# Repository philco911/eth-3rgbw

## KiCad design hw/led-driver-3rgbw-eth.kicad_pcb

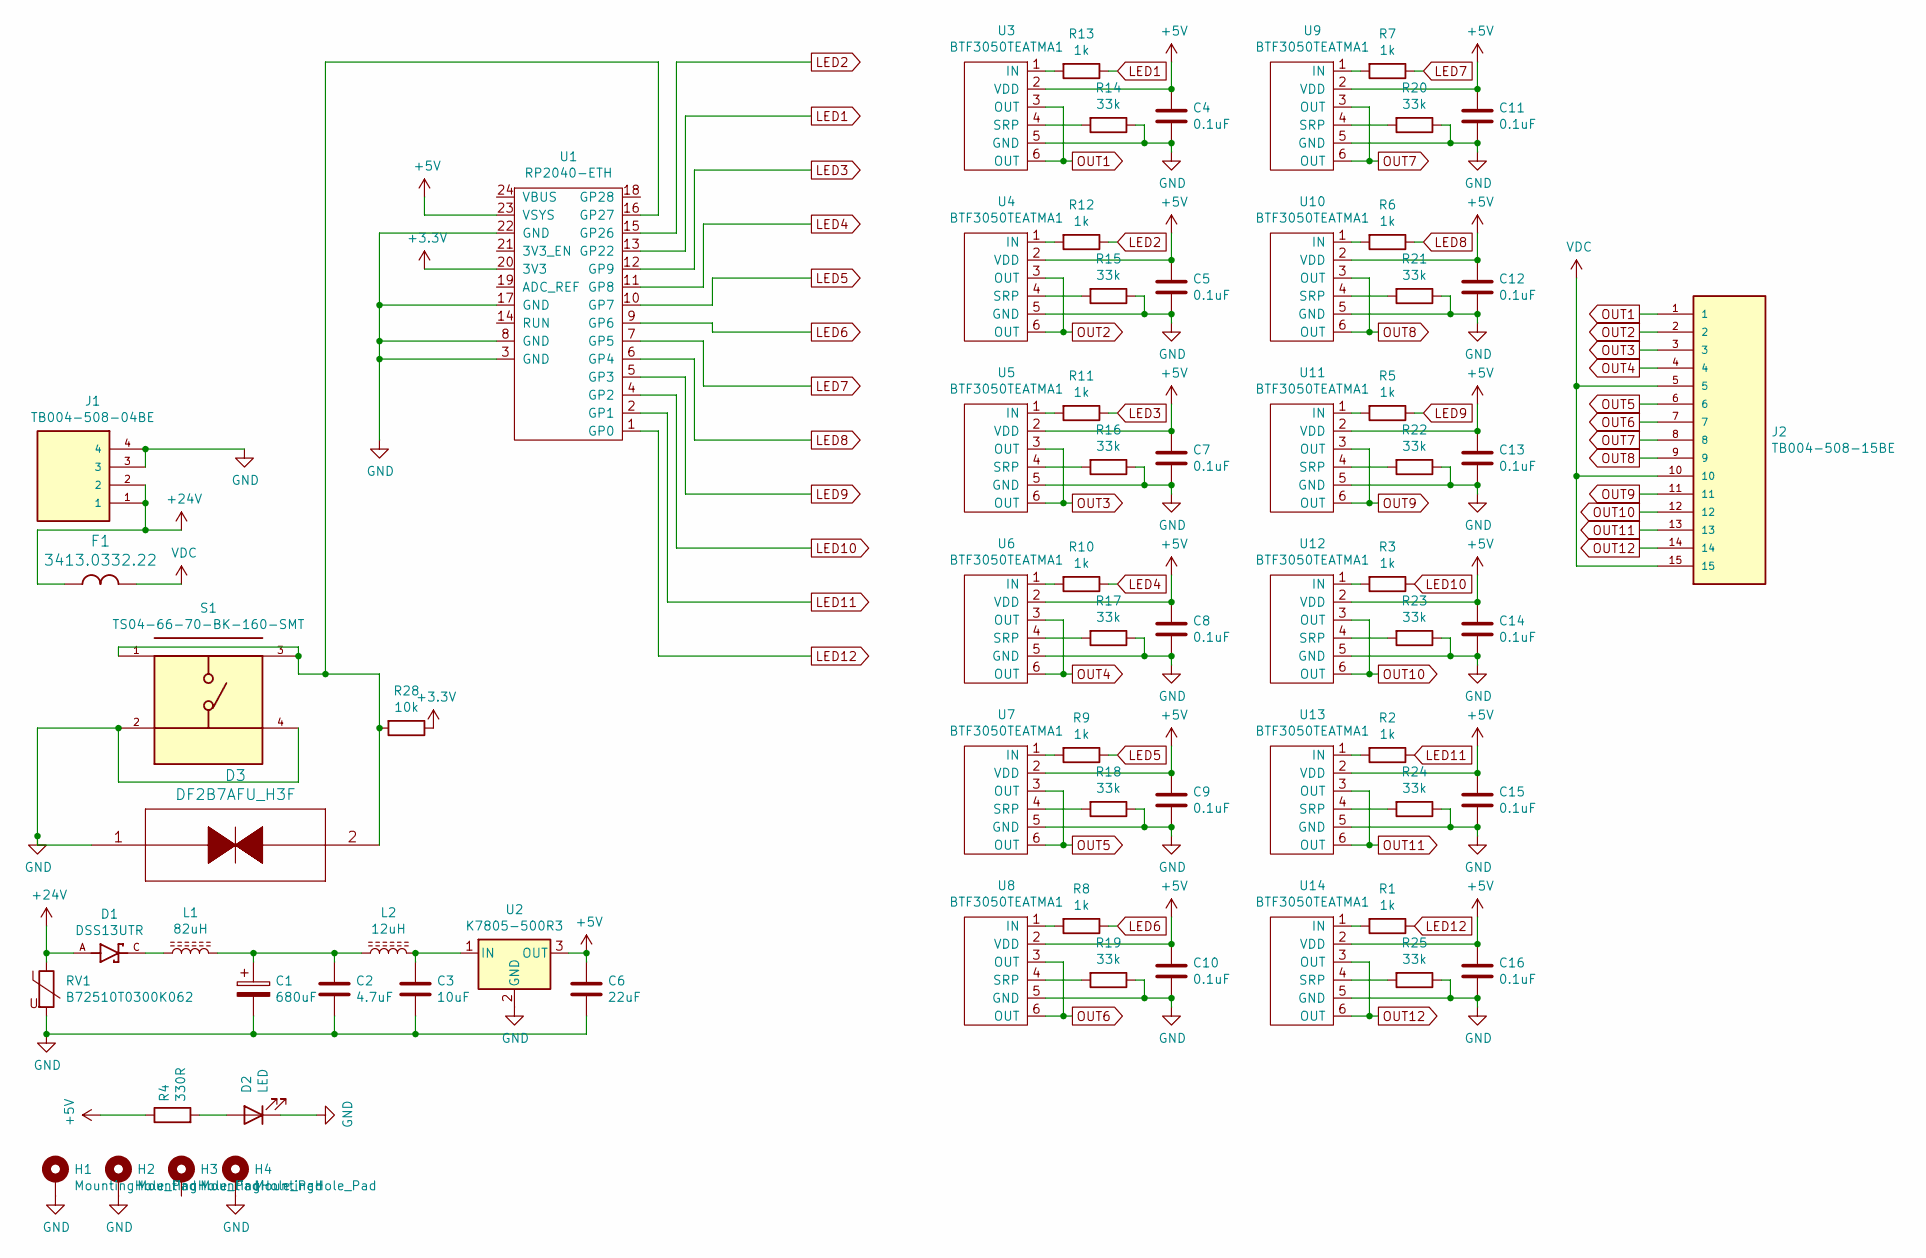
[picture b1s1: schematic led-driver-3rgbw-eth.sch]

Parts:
C1: 680uF; CP_Radial_D12.5mm_P5.00mm
C2: 4.7uF; C_0805_2012Metric
C3: 10uF; C_0805_2012Metric
C4, C5, C7, C8, C9, C10, C11, C12, C13, C14, C15, C16: 0.1uF; C_0805_2012Metric
C6: 22uF; C_0805_2012Metric
D1: DSS13UTR; SODFL3618X110N
D2: LED; LED_0805_2012Metric
D3: DF2B7AFU_H3F
F1: 3413.0332.22
H1, H2, H3, H4: MountingHole_Pad; MountingHole_3mm_Pad
J1: TB004-508-04BE; CUI_TB004-508-04BE
J2: TB004-508-15BE; CUI_TB004-508-15BE
L1: 82uH; IND_B1047AS-820M=P3
L2: 12uH; IND_1229AS-H-120M=P3
R1, R2, R3, R5, R6, R7, R8, R9, R10, R11, R12, R13: 1k; R_0805_2012Metric
R4: 330R; R_0805_2012Metric
R14, R15, R16, R17, R18, R19, R20, R21, R22, R23, R24, R25: 33k; R_0805_2012Metric
R28: 10k; R_0805_2012Metric
RV1: B72510T0300K062; R_0805_2012Metric
S1: TS04-66-70-BK-160-SMT; SW_TS04-66-70-BK-160-SMT; PARTREV 1.0
U1: RP2040-ETH; DIP-24_1824_ELL
U2: K7805-500R3; CONV_K7805-500R3
U3, U4, U5, U6, U7, U8, U9, U10, U11, U12, U13, U14: BTF3050TEATMA1; TO-252-5_TabPin6

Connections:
+3V3: R28.1, U1.20 (3V3)
+5V: C4.1, C5.1, C6.1, C7.1, C8.1, C9.1, C10.1, C11.1, C12.1, C13.1, C14.1, C15.1, C16.1, R4.1, U1.23 (VSYS), U2.3 (OUT), U3.2 (VDD), U4.2 (VDD), U5.2 (VDD), U6.2 (VDD), U7.2 (VDD), U8.2 (VDD), U9.2 (VDD), U10.2 (VDD), U11.2 (VDD), U12.2 (VDD), U13.2 (VDD), U14.2 (VDD)
+24V: D1.A, F1.1, J1.1, J1.2, RV1.1
GND: C1.2, C2.2, C3.2, C4.2, C5.2, C6.2, C7.2, C8.2, C9.2, C10.2, C11.2, C12.2, C13.2, C14.2, C15.2, C16.2, D2.1 (K), D3.1 (PIN1), H1.1, H2.1, H4.1, J1.3, J1.4, R14.1, R15.1, R16.1, R17.1, R18.1, R19.1, R20.1, R21.1, R22.1, R23.1, R24.1, R25.1, RV1.2, S1.2, S1.4, U1.3 (GND), U1.8 (GND), U1.17 (GND), U1.22 (GND), U2.2 (GND), U3.5 (GND), U4.5 (GND), U5.5 (GND), U6.5 (GND), U7.5 (GND), U8.5 (GND), U9.5 (GND), U10.5 (GND), U11.5 (GND), U12.5 (GND), U13.5 (GND), U14.5 (GND)
LED1: R13.1, U1.13 (GP22)
LED2: R12.1, U1.15 (GP26)
LED3: R11.1, U1.12 (GP9)
LED4: R10.1, U1.11 (GP8)
LED5: R9.1, U1.10 (GP7)
LED6: R8.1, U1.9 (GP6)
LED7: R7.1, U1.7 (GP5)
LED8: R6.1, U1.6 (GP4)
LED9: R5.1, U1.5 (GP3)
LED10: R3.1, U1.4 (GP2)
LED11: R2.1, U1.2 (GP1)
LED12: R1.1, U1.1 (GP0)
unnamed: C1.1, C2.1, L1.2, L2.1
unnamed: C3.1, L2.2, U2.1 (IN)
unnamed: D1.C, L1.1
unnamed: D2.2 (A), R4.2
unnamed: D3.2 (PIN2), R28.2, S1.1, S1.3, U1.16 (GP27)
unnamed: R1.2, U14.1 (IN)
unnamed: R2.2, U13.1 (IN)
unnamed: R3.2, U12.1 (IN)
unnamed: R5.2, U11.1 (IN)
unnamed: R6.2, U10.1 (IN)
unnamed: R7.2, U9.1 (IN)
unnamed: R8.2, U8.1 (IN)
unnamed: R9.2, U7.1 (IN)
unnamed: R10.2, U6.1 (IN)
unnamed: R11.2, U5.1 (IN)
unnamed: R12.2, U4.1 (IN)
unnamed: R13.2, U3.1 (IN)
unnamed: R14.2, U3.4 (SRP)
unnamed: R15.2, U4.4 (SRP)
unnamed: R16.2, U5.4 (SRP)
unnamed: R17.2, U6.4 (SRP)
unnamed: R18.2, U7.4 (SRP)
unnamed: R19.2, U8.4 (SRP)
unnamed: R20.2, U9.4 (SRP)
unnamed: R21.2, U10.4 (SRP)
unnamed: R22.2, U11.4 (SRP)
unnamed: R23.2, U12.4 (SRP)
unnamed: R24.2, U13.4 (SRP)
unnamed: R25.2, U14.4 (SRP)
OUT1: J2.1, U3.3 (OUT), U3.6 (OUT)
OUT2: J2.2, U4.3 (OUT), U4.6 (OUT)
OUT3: J2.3, U5.3 (OUT), U5.6 (OUT)
OUT4: J2.4, U6.3 (OUT), U6.6 (OUT)
OUT5: J2.6, U7.3 (OUT), U7.6 (OUT)
OUT6: J2.7, U8.3 (OUT), U8.6 (OUT)
OUT7: J2.8, U9.3 (OUT), U9.6 (OUT)
OUT8: J2.9, U10.3 (OUT), U10.6 (OUT)
OUT9: J2.11, U11.3 (OUT), U11.6 (OUT)
OUT10: J2.12, U12.3 (OUT), U12.6 (OUT)
OUT11: J2.13, U13.3 (OUT), U13.6 (OUT)
OUT12: J2.14, U14.3 (OUT), U14.6 (OUT)
VDC: F1.2, J2.5, J2.10, J2.15

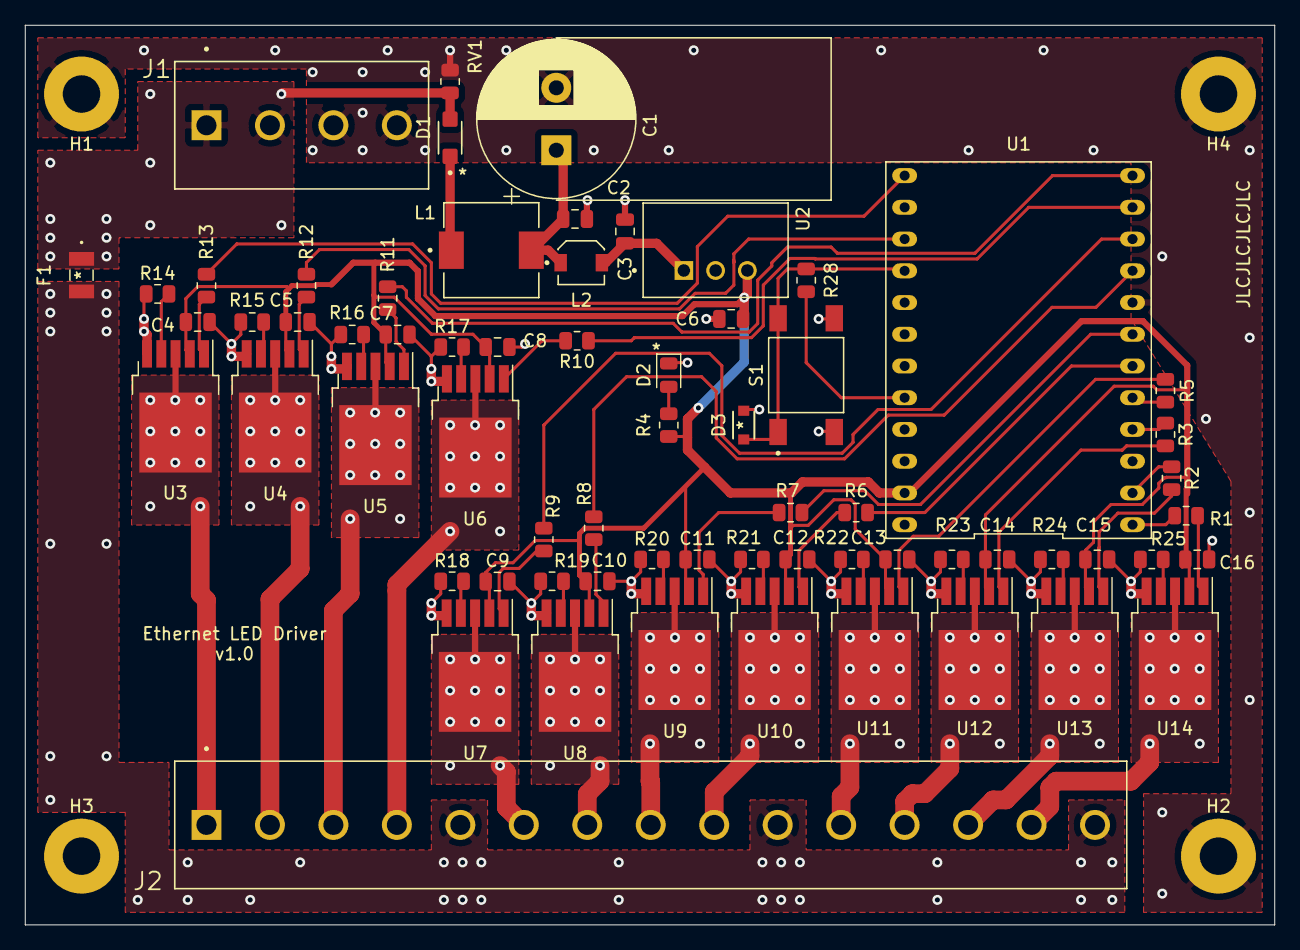
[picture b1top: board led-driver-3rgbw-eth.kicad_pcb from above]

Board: 2 copper layers, 100.0 x 72.0 mm, 70 parts (0 on the bottom side), 58 nets.

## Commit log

2023-07-13 Initial import of 3rgbw project

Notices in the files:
parts and their libraries:
Copyright 2021 Accelerated Designs. All rights reserved.
Copyright 2016 Accelerated Designs. All rights reserved.
